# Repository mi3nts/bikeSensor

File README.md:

# Bike Bottle Design Overview
## Introduction 
Portable devices which can detect airbourne particulates are finding its way into current consumer markets. Unlike there bulky, stationary counterparts the small scale nature of such sensors feeds into a more user friendly, hazzle free platform. The current document proposes such a portable device designed to be fit within a bike bottle housing. Particulate matter is linked with a number of negative health outcomes. Such links are to be addressed with the use of the propesed device.

### Design Specifications  

#### Absolute Necessities 
1. Main Housing:
 - The enclosed device should fit a bike bottle housing.

2. OPC Sensor: 
 - Must have the Alhpa Sense OPC-N3 <br/>
   **http://www.alphasense.com/WEB1213/wp-content/uploads/2018/02/OPC-N3.pdf** <br/>      

3. Automated Notifications 
 - Should sound an alarm when passing through dirty air. 

4. Secondary Sensors: 
- Must have Temprature, Humidity, Pressure and GPS sensors.   

5. Battery:
- Must contain a rechargable portable battery which will enable the device to stay on for atleast for 4 hours.
- Must have an indicator which shows the status of the battery Charge.
- Should be able to work 24*7 when connected to power(Charging pod).

6. Date Storage: 
- The device should be capable of storing at least 24 hours of Data.  
- The Storage output should be a csv 
- Should be accessible to the end user 

7. Weight 
- Must weigh less than 1 Kg.

8. Cost 
- The Whole sensor should cost less than 2000$.

##### Attractive Addons 

1. Secondary Sensors: 
- Inclusion of gas sensors such as NO2 (Nitrogen Dioxide), O3 (Ozone), CO (Carbon Monoxide), SO2 (Sulfer Dioxide), and H2S (Hydrogen Sulfide). 

2. Battery:
- A portable battery which will enable the device to stay on for atleast **24 hours** per charge.

3. Date Storage: 
- Automated Cloud link

4. Mobile App
- Inclusion of an andorid/ios app which will give out live statistics from the data collected.

5. Weight 
- Weigh less than 500g.

6. Cost 
- Getting the cost to be less than 1000$.

7. Wireless Connectivity 
- Inlcussion of a wireless modem and have the possibiilty of WiFi.

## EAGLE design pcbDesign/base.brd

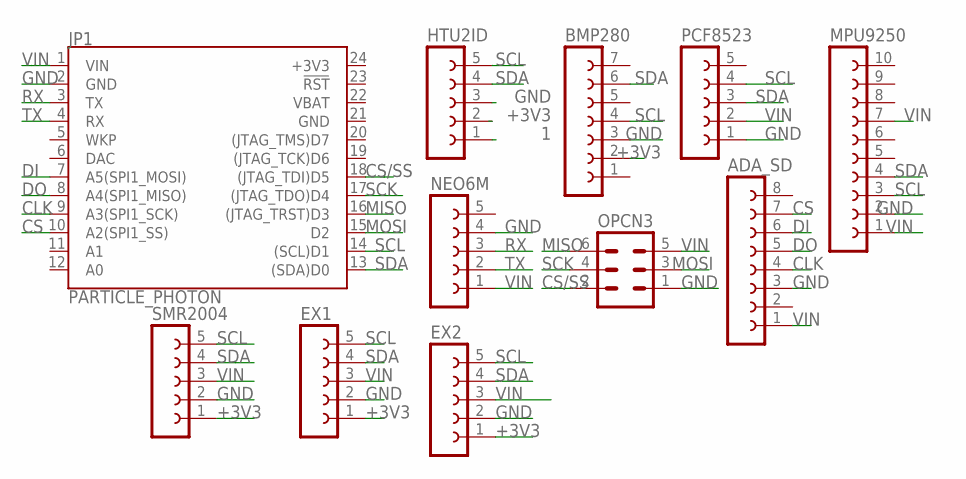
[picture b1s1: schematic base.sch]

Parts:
ADA_SD: FE08-1; FE08
BMP280: FE07-1; FE07
EX1, EX2: FE05-1
HTU2ID: FE05-1
JP1: PARTICLE_PHOTON
MPU9250: FE10-1; FE10
NEO6M: FE05-1
OPCN3: MA03-2
PCF8523: FE05-1
SMR2004: FE05-1

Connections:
1: HTU2ID.1
+3V3: BMP280.2, EX1.1, EX2.1, HTU2ID.2, JP1.24 (+3V3), SMR2004.1
CLK: ADA_SD.4, JP1.9 (A3(SPI1_SCK))
CS: ADA_SD.7, JP1.10 (A2(SPI1_SS))
CS/SS: JP1.18 ((JTAG_TDI)D5), OPCN3.2
DI: ADA_SD.6, JP1.7 (A5(SPI1_MOSI))
DO: ADA_SD.5, JP1.8 (A4(SPI1_MISO))
GND: ADA_SD.3, BMP280.3, EX1.2, EX2.2, HTU2ID.3, JP1.2 (GND), JP1.21 (GND), MPU9250.2, NEO6M.4, OPCN3.1, PCF8523.1, SMR2004.2
MISO: JP1.16 ((JTAG_TRST)D3), OPCN3.6
MOSI: JP1.15 (D2), OPCN3.3
RX: JP1.3 (TX), NEO6M.3
SCK: JP1.17 ((JTAG_TDO)D4), OPCN3.4
SCL: BMP280.4, EX1.5, EX2.5, HTU2ID.5, JP1.14 ((SCL)D1), MPU9250.3, PCF8523.4, SMR2004.5
SDA: BMP280.6, EX1.4, EX2.4, HTU2ID.4, JP1.13 ((SDA)D0), MPU9250.4, PCF8523.3, SMR2004.4
TX: JP1.4 (RX), NEO6M.2
VBAT: JP1.22 (VBAT)
VIN: ADA_SD.1, EX1.3, EX2.3, JP1.1 (VIN), MPU9250.1, MPU9250.7, NEO6M.1, OPCN3.5, PCF8523.2, SMR2004.3

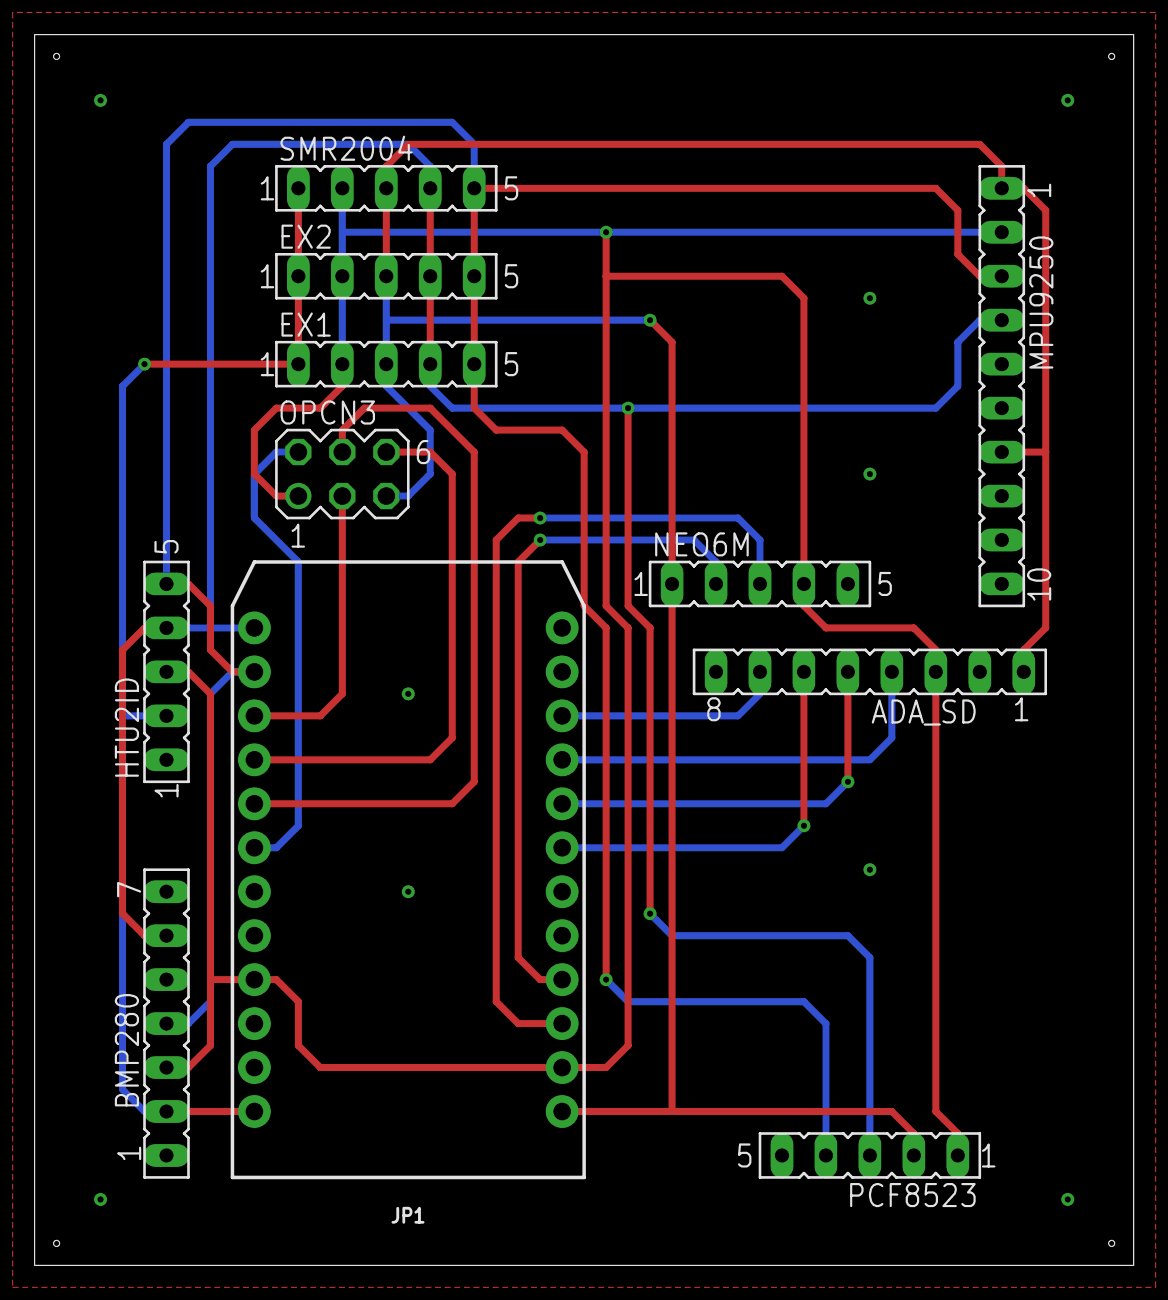
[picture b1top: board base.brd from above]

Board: 2 copper layers, 63.5 x 71.1 mm, 11 parts (0 on the bottom side), 15 nets.

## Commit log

2018-10-06 Updating Bike Sensor repos
2018-11-09 Daily Updates
2018-11-19 Rename Overview.md to reamMe.md
2018-11-19 Rename README.md to readMe.md

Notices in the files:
parts and their libraries:
SparkFun-Boards: Licensing: Creative Commons ShareAlike 4.0 International - https://creativecommons.org/licenses/by-sa/4.0
